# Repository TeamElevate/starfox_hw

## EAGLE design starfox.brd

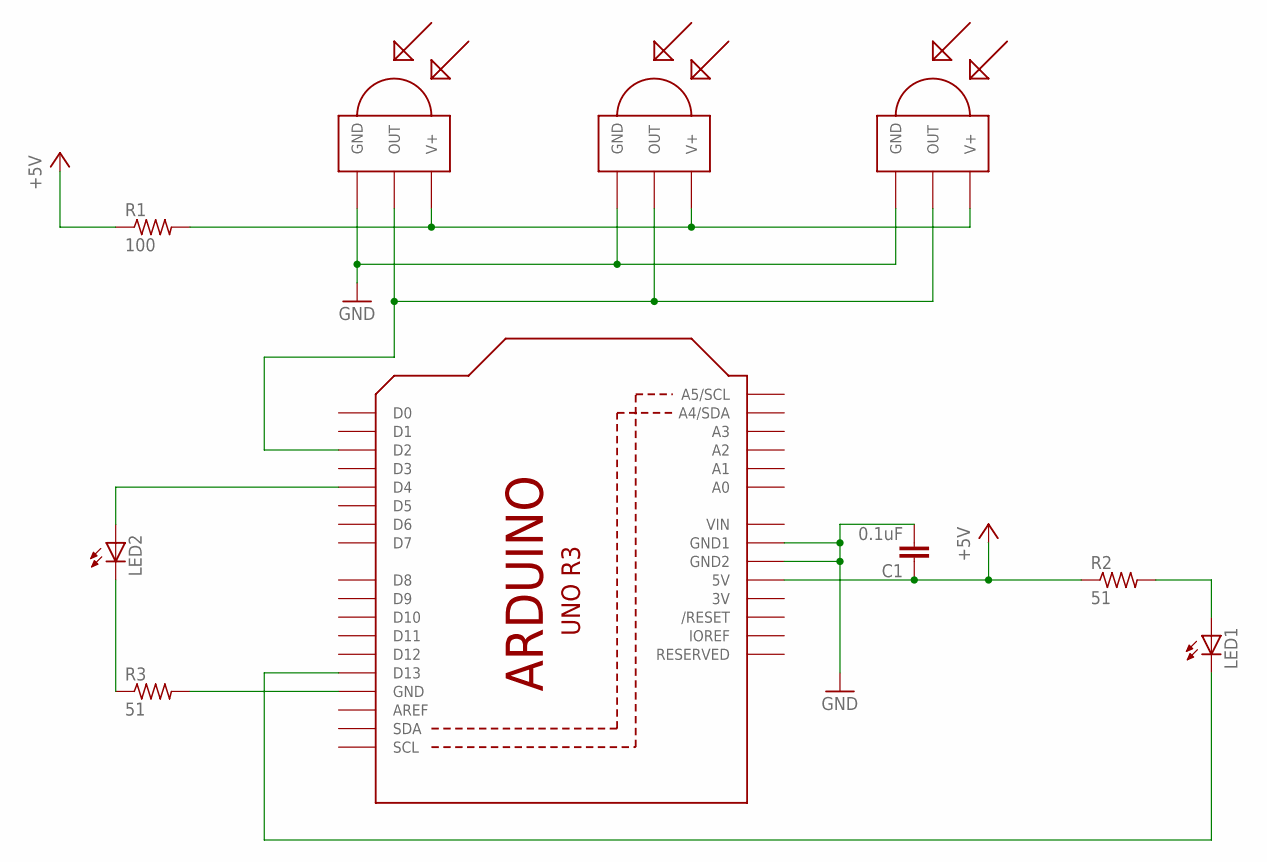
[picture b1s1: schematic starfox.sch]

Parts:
C1: 0.1uF; C025-025X050
LED1, LED2: LED5MM
R1: 100; 0204/7
R2, R3: 51; 0204/7
U1: ARDUINOR3-DIMENSION; ARDUINOR3
U$1, U$2, U$3: TSOP4836; TSOP18XX

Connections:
3V: U1.3V
+5V: C1.1, R1.1, R2.1, U1.5V
GND: C1.2, U1.GND1, U1.GND2, U$1.GND, U$2.GND, U$3.GND
unnamed: R1.2, U$1.VCC (V+), U$2.VCC (V+), U$3.VCC (V+)
unnamed: U1.D2, U$1.OUT, U$2.OUT, U$3.OUT
unnamed: LED1.A, R2.2
unnamed: LED1.K (C), U1.D13
unnamed: LED2.A, U1.D4
unnamed: LED2.K (C), R3.1
unnamed: R3.2, U1.GND
VIN: U1.VIN

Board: 2 copper layers, 10 parts (0 on the bottom side), 9 nets, no tracks yet.

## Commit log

2014-10-16 [Init] Initial commit
2014-10-16 Adding libraries
